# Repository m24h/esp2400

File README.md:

# esp2400

A digitalizing power supply control board woking with modified ZXD2400 (50V 50A) modoule.

This project is a control board mainly using ESP32 as core MPU, with ST7789V display,
including software source codes, hardware design, and other parts design,
to control a simply modified ZXD2400 power supply module.

In fact, this project is suitable for modifying other power supply module too.

its main functions include:
. 0-50.00V and 0-50.00A output with internal 14bits resolution
. Multi-points calibration of voltage and current.
. Two EC11 rotaries to control voltage and current separately
. Multi quick-pick of voltage and current by single pressing button
. Statistics by seconds, minutes, hours
. WIFI STA and AP support with a simple web view for remote control
. Command line support with USB-Serial interface (also firmware updating interface)
. Temperature controlled FAN output using PID algorithm
. A discharging circuit to decrease dormancy of switching power supply at low-voltage outputing
. Rate of rising and falling of voltage and current can be controlled
. Chinese and English bundles support (but in fact, original ZXD2400 with its PFC circiut can be used in AC220V zones)

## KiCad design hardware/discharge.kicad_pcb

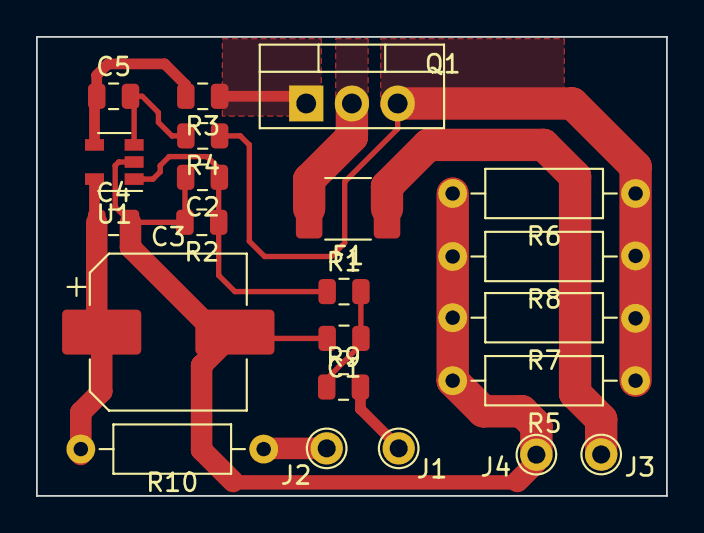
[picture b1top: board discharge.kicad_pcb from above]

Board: 2 copper layers, 35.0 x 25.5 mm, 22 parts (0 on the bottom side), 12 nets.

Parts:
C1: 0.47; C_0805_2012Metric
C2: 1; C_0805_2012Metric
C3: 100/25v; CP_Elec_8x10.5
C4: 0.1; C_0805_2012Metric
C5: 2n; C_0805_2012Metric
F1: 2.6A; Fuse_1812_4532Metric_Castellated
J1, J2, J3, J4: PAD; Pad
Q1: FHP40N20; TO-220-3_Vertical
R1, R4, R9: 10k; R_0805_2012Metric
R2: 2.2k; R_0805_2012Metric
R3: 1k; R_0805_2012Metric
R5, R7: 1/0.25w; R_Axial_DIN0207_L6.3mm_D2.5mm_P10.16mm_Horizontal
R6, R8: 1/0.25W; R_Axial_DIN0207_L6.3mm_D2.5mm_P10.16mm_Horizontal
R10: 47/0.25W; R_Axial_DIN0207_L6.3mm_D2.5mm_P10.16mm_Horizontal
U1: LM321; SOT-23-5

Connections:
unnamed: C1.1, R1.2, R9.1
unnamed: C1.2, C2.2, C3.2, C4.2, J4.1, R2.2, R5.2, R6.2, R7.2, R8.2, U1.2
unnamed: C2.1, R1.1, R2.1, U1.1
unnamed: C3.1, C4.1, R10.2, U1.5
unnamed: C5.1, R3.2, U1.4
unnamed: C5.2, R4.2, U1.3
unnamed: F1.1, J3.1
unnamed: F1.2, Q1.2
unnamed: J1.1, R9.2
unnamed: J2.1, R10.1
unnamed: Q1.1, R3.1
unnamed: Q1.3, R4.1, R5.1, R6.1, R7.1, R8.1

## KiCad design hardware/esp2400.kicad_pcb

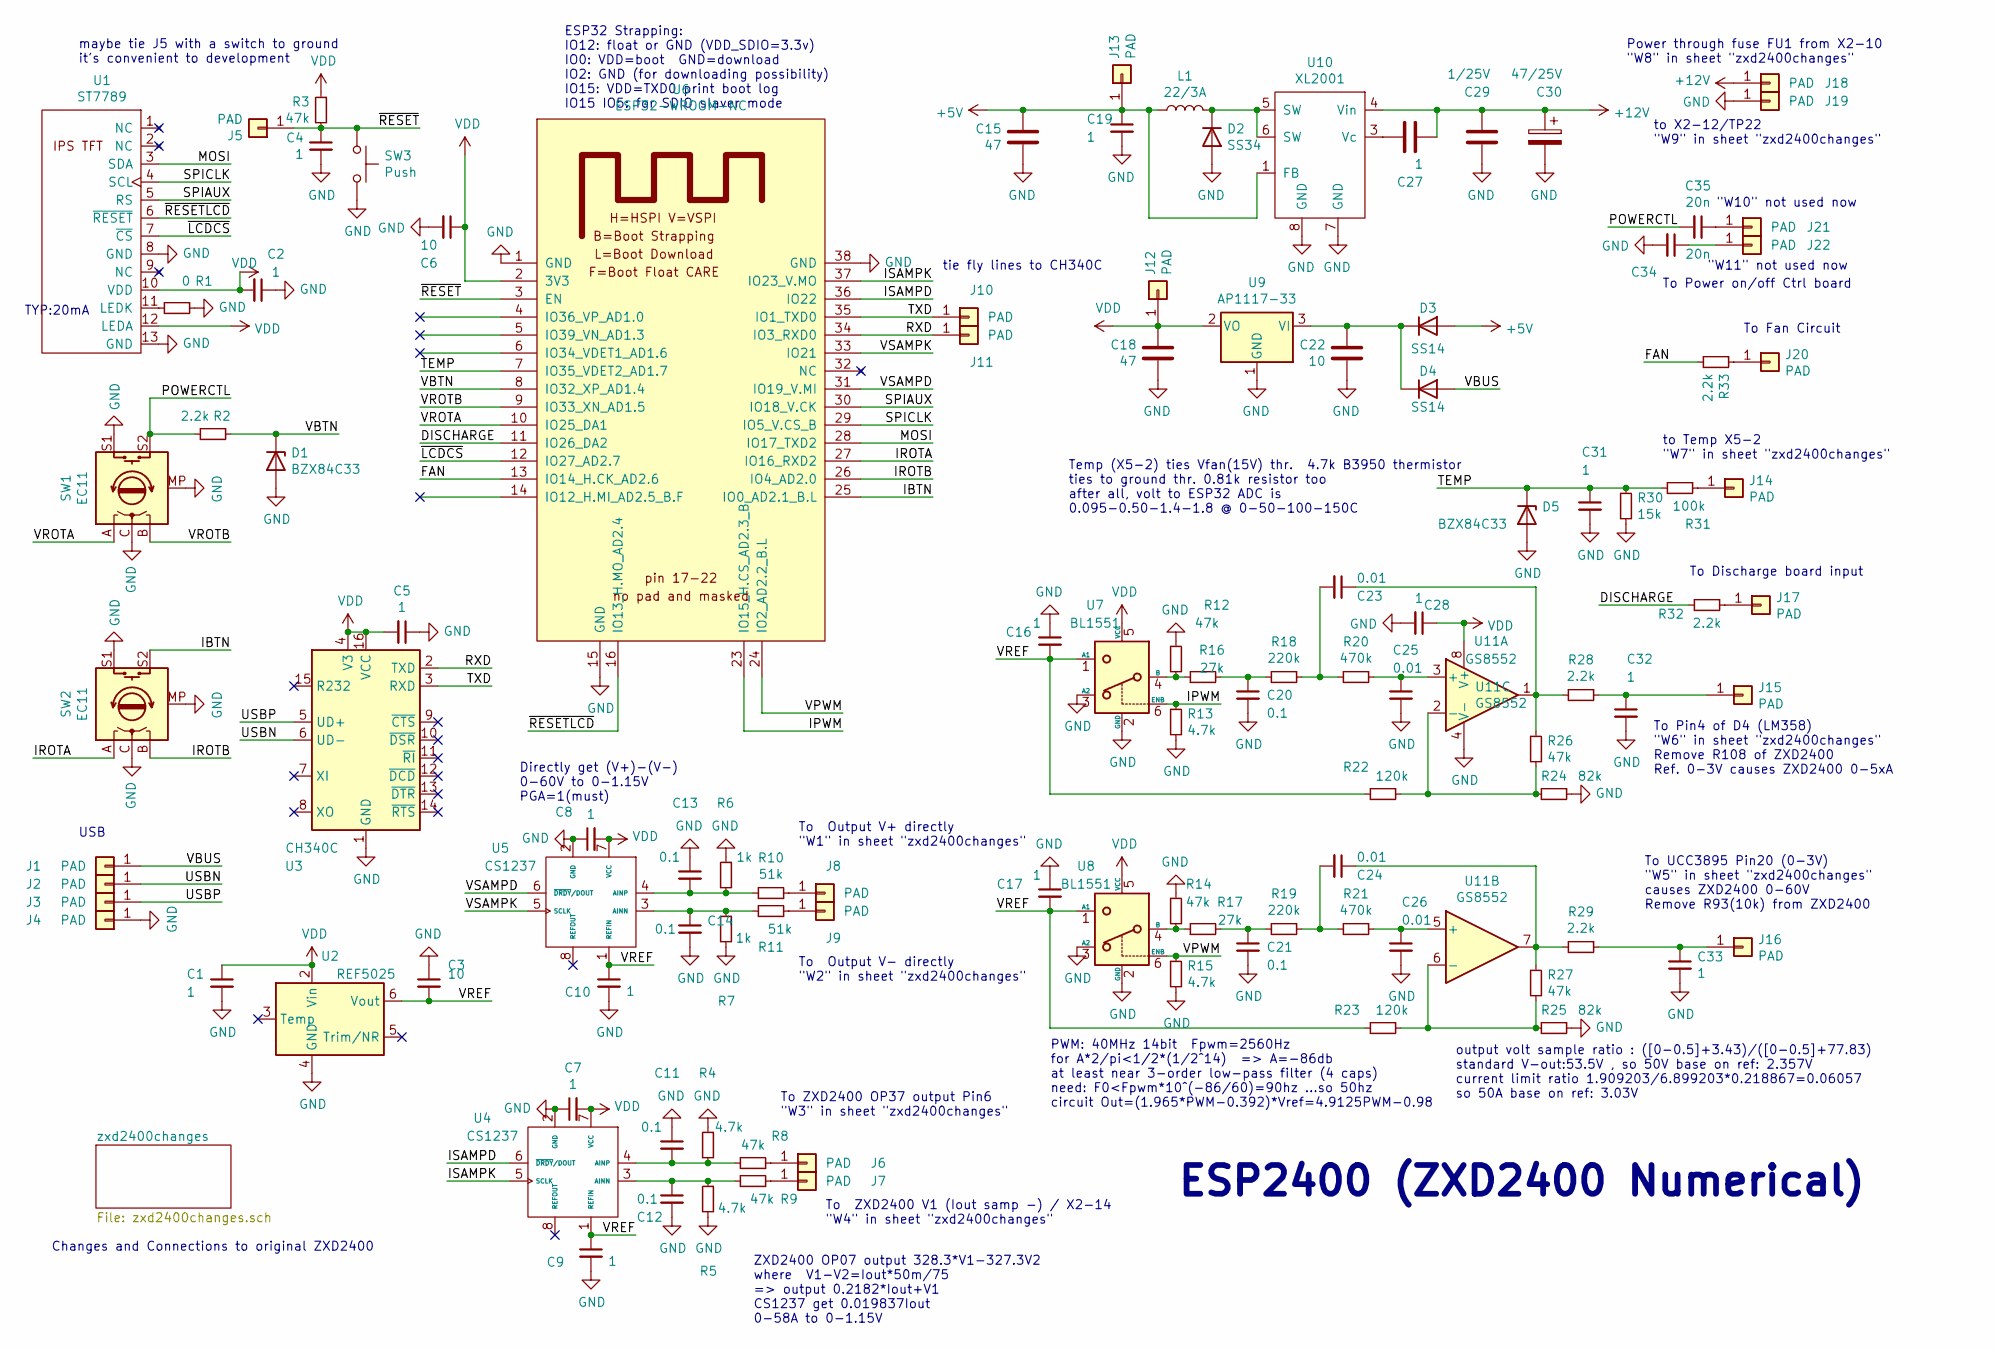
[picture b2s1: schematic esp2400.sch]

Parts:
C1, C2, C4, C5, C7, C8, C9, C10, C16, C17, C19, C27, C28, C31, C32, C33: 1; C_0805_2012Metric
C3, C6, C22: 10; C_0805_2012Metric
C11, C12, C13, C14, C20, C21: 0.1; C_0603_1608Metric
C15, C18: 47; C_1210_3225Metric
C23, C24, C25, C26: 0.01; C_0603_1608Metric
C29: 1/25V; C_1206_3216Metric
C30: 47/25V; CP_Elec_5x5.9
C34, C35: 20n; C_0805_2012Metric
D1, D5: BZX84C33; D_SOT-23_ANK
D2: SS34; D_SMB
D3, D4: SS14; D_SMA
J1, J2, J3, J4, J5, J6, J7, J8, J9, J10, J11, J12, J13, J14, J15, J16, J17, J18, J19, J20, J21, J22: PAD; Pad
L1: 22/3A; L_Bourns_SRP7028A_7.3x6.6mm
R1: 0; R_0805_2012Metric
R2, R28, R29, R32, R33: 2.2k; R_0603_1608Metric
R3, R8, R9, R12, R14, R26, R27: 47k; R_0603_1608Metric
R4, R5, R13, R15: 4.7k; R_0603_1608Metric
R6, R7: 1k; R_0603_1608Metric
R10, R11: 51k; R_0603_1608Metric
R16, R17: 27k; R_0603_1608Metric
R18, R19: 220k; R_0603_1608Metric
R20, R21: 470k; R_0603_1608Metric
R22, R23: 120k; R_0603_1608Metric
R24, R25: 82k; R_0603_1608Metric
R30: 15k; R_0603_1608Metric
R31: 100k; R_0603_1608Metric
SW1, SW2: EC11; RotaryEncoder_Alps_EC11E-Switch_Vertical_H20mm
SW3: Push; SW_Push_1P1T_NO_CK_KSC6xxJ
U1: ST7789; 1.14LCD
U2: REF5025; SOIC-8_3.9x4.9mm_P1.27mm
U3: CH340C; SOP-16_4.4x10.4mm_P1.27mm
U4, U5: CS1237; SOP-8_3.9x4.9mm_P1.27mm
U6: ESP32-WROOM-NC
U7, U8: BL1551; SC70-6
U9: AP1117-33; SOT-223-3_TabPin2
U10: XL2001; SOIC-8_3.9x4.9mm_P1.27mm
U11: GS8552; SOIC-8_3.9x4.9mm_P1.27mm

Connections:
+5V: C15.1, C19.1, D3.2 (A), J13.1, L1.2, U10.1 (FB)
+12V: C27.2, C29.1, C30.1, J18.1, U10.4 (Vin)
/DISCHARGE: R32.2, U6.11 (IO26_DA2)
/FAN: R33.2, U6.13 (IO14_H.CK_AD2.6)
/IBTN: SW2.S2, U6.25 (IO0_AD2.1_B.L)
/IPWM: R13.1, U6.23 (IO15_H.CS_AD2.3_B), U7.6 (ENB)
/IROTA: SW2.A, U6.27 (IO16_RXD2)
/IROTB: SW2.B, U6.26 (IO4_AD2.0)
/ISAMPD: U4.6 (~DRDY~/DOUT), U6.36 (IO22)
/ISAMPK: U4.5 (SCLK), U6.37 (IO23_V.MO)
/MOSI: U1.3 (SDA), U6.28 (IO17_TXD2)
/POWERCTL: C35.2, R2.2, SW1.S2
/RXD: J11.1, U3.2 (TXD), U6.34 (IO3_RXD0)
/SPIAUX: U1.5 (RS), U6.30 (IO18_V.CK)
/SPICLK: U1.4 (SCL), U6.29 (IO5_V.CS_B)
/TEMP: C31.1, D5.1 (K), R30.1, R31.2, U6.7 (IO35_VDET2_AD1.7)
/TXD: J10.1, U3.3 (RXD), U6.35 (IO1_TXD0)
/USBN: J2.1, U3.6 (UD-)
/USBP: J3.1, U3.5 (UD+)
/VBTN: D1.1 (K), R2.1, U6.8 (IO32_XP_AD1.4)
/VBUS: D4.2 (A), J1.1
/VPWM: R15.1, U6.24 (IO2_AD2.2_B.L), U8.6 (ENB)
/VREF: C3.2, C9.1, C10.1, C16.2, C17.2, R22.2, R23.2, U2.6 (Vout), U4.1 (REFIN), U5.1 (REFIN), U7.1 (A1), U8.1 (A1)
/VROTA: SW1.A, U6.10 (IO25_DA1)
/VROTB: SW1.B, U6.9 (IO33_XN_AD1.5)
/VSAMPD: U5.6 (~DRDY~/DOUT), U6.31 (IO19_V.MI)
/VSAMPK: U5.5 (SCLK), U6.33 (IO21)
/~LCDCS: U1.7 (~CS), U6.12 (IO27_AD2.7)
/~RESET: C4.1, J5.1, R3.2, SW3.1, U6.3 (EN)
/~RESETLCD: U1.6 (~RESET), U6.16 (IO13_H.MO_AD2.4)
GND: C1.2, C2.1, C3.1, C4.2, C5.1, C6.2, C7.1, C8.1, C9.2, C10.2, C11.1, C12.2, C13.1, C14.2, C15.2, C16.1, C17.1, C18.2, C19.2, C20.2, C21.2, C22.2, C25.2, C26.2, C28.2, C29.2, C30.2, C31.2, C32.2, C33.2, C34.2, D1.2 (A), D2.2 (A), D5.2 (A), J4.1, J19.1, R1.1, R4.1, R5.2, R6.1, R7.2, R12.1, R13.2, R14.1, R15.2, R24.1, R25.1, R30.2, SW1.C, SW1.MP, SW1.S1, SW2.C, SW2.MP, SW2.S1, SW3.2, U1.8 (GND), U1.13 (GND), U2.4 (GND), U3.1 (GND), U4.2 (GND), U5.2 (GND), U6.1 (GND), U6.15 (GND), U6.38 (GND), U7.2 (GND), U7.3 (A2), U8.2 (GND), U8.3 (A2), U9.1 (GND), U10.7 (GND), U10.8 (GND), U11.4 (V-)
unnamed: C11.2, R4.2, R8.2, U4.4 (AINP)
unnamed: C12.1, R5.1, R9.2, U4.3 (AINN)
unnamed: C13.2, R6.2, R10.2, U5.4 (AINP)
unnamed: C14.1, R7.1, R11.2, U5.3 (AINN)
unnamed: C20.1, R16.2, R18.2
unnamed: C21.1, R17.2, R19.2
unnamed: C22.1, D3.1 (K), D4.1 (K), U9.3 (VI)
unnamed: C23.1, R26.1, R28.2, U11.1
unnamed: C23.2, R18.1, R20.2
unnamed: C24.1, R27.1, R29.2, U11.7
unnamed: C24.2, R19.1, R21.2
unnamed: C25.1, R20.1, U11.3 (+)
unnamed: C26.1, R21.1, U11.5 (+)
unnamed: C27.1, U10.3 (Vc)
unnamed: C32.1, J15.1, R28.1
unnamed: C33.1, J16.1, R29.1
unnamed: C34.1, J22.1
unnamed: C35.1, J21.1
unnamed: D2.1 (K), L1.1, U10.5 (SW), U10.6 (SW)
unnamed: J6.1, R8.1
unnamed: J7.1, R9.1
unnamed: J8.1, R10.1
unnamed: J9.1, R11.1
unnamed: J14.1, R31.1
unnamed: J17.1, R32.1
unnamed: J20.1, R33.1
unnamed: R1.2, U1.11 (LEDK)
unnamed: R12.2, R16.1, U7.4 (B)
unnamed: R14.2, R17.1, U8.4 (B)
unnamed: R22.1, R24.2, R26.2, U11.2 (-)
unnamed: R23.1, R25.2, R27.2, U11.6 (-)
VDD: C1.1, C2.2, C5.2, C6.1, C7.2, C8.2, C18.1, C28.1, J12.1, R3.1, U1.10 (VDD), U1.12 (LEDA), U2.2 (Vin), U3.4 (V3), U3.16 (VCC), U4.7 (VCC), U5.7 (VCC), U6.2 (3V3), U7.5 (VCC), U8.5 (VCC), U9.2 (VO), U11.8 (V+)

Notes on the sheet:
TYP:20mA
Power through fuse FU1 from X2-10 "W8" in sheet "zxd2400changes"
To Fan Circuit
to X2-12/TP22 "W9" in sheet "zxd2400changes"
To Discharge board input
To UCC3895 Pin20 (0-3V) "W5" in sheet "zxd2400changes" causes ZXD2400 0-60V Remove R93(10k) from ZXD2400
ESP32 Strapping: IO12: float or GND (VDD_SDIO=3.3v) IO0: VDD=boot GND=download IO2: GND (for downloading possibility) IO15: VDD=TXD0 print boot log IO15 IO5: for SDIO slaver mode
PWM: 40MHz 14bit Fpwm=2560Hz for A*2/pi<1/2*(1/2^14) => A=-86db at least near 3-order low-pass filter (4 caps) need: F0<Fpwm*10^(-86/60)=90hz ...so 50hz circuit Out=(1.965*PWM-0.392)*Vref=4.9125PWM-0.98
To Output V+ directly "W1" in sheet "zxd2400changes"
To Output V- directly "W2" in sheet "zxd2400changes"
To ZXD2400 OP37 output Pin6 "W3" in sheet "zxd2400changes"
To ZXD2400 V1 (Iout samp -) / X2-14 "W4" in sheet "zxd2400changes"
Directly get (V+)-(V-) 0-60V to 0-1.15V PGA=1(must)
ZXD2400 OP07 output 328.3*V1-327.3V2 where V1-V2=Iout*50m/75 => output 0.2182*Iout+V1 CS1237 get 0.019837Iout 0-58A to 0-1.15V
To Power on/off Ctrl board
ESP2400 (ZXD2400 Numerical)
to Temp X5-2 "W7" in sheet "zxd2400changes"
To Pin4 of D4 (LM358) "W6" in sheet "zxd2400changes" Remove R108 of ZXD2400 Ref. 0-3V causes ZXD2400 0-5xA
USB
Temp (X5-2) ties Vfan(15V) thr. 4.7k B3950 thermistor ties to ground thr. 0.81k resistor too after all, volt to ESP32 ADC is 0.095-0.50-1.4-1.8 @ 0-50-100-150C
output volt sample ratio : ([0-0.5]+3.43)/([0-0.5]+77.83) standard V-out:53.5V , so 50V base on ref: 2.357V current limit ratio 1.909203/6.899203*0.218867=0.06057 so 50A base on ref: 3.03V
Changes and Connections to original ZXD2400
maybe tie J5 with a switch to ground it's convenient to development
tie fly lines to CH340C
"W10" not used now
"W11" not used now

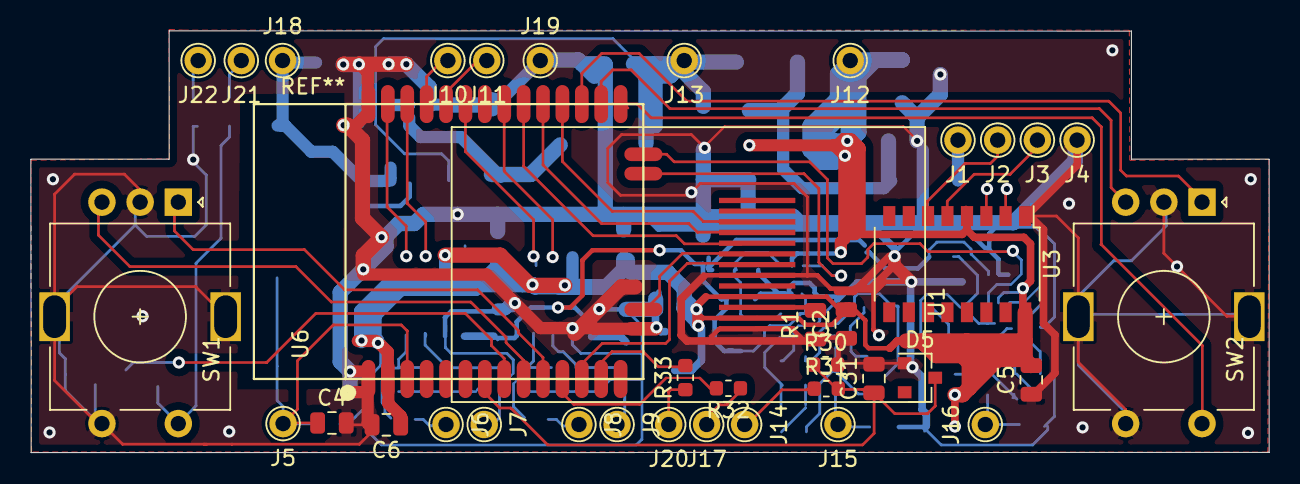
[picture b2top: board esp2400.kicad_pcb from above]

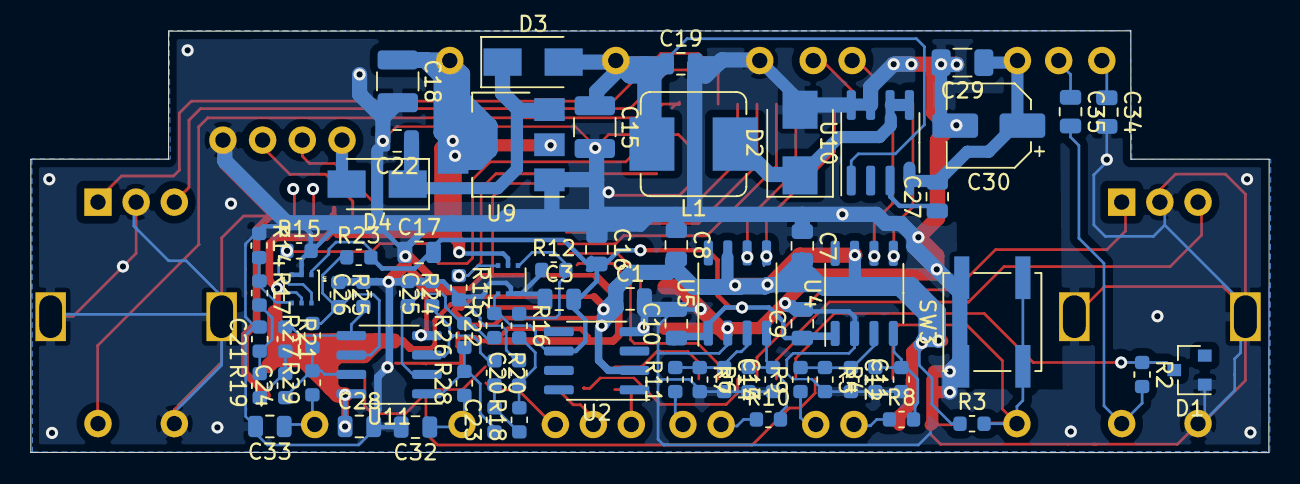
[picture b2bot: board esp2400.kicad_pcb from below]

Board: 2 copper layers, 81.1 x 27.6 mm, 110 parts (72 on the bottom side), 63 nets.

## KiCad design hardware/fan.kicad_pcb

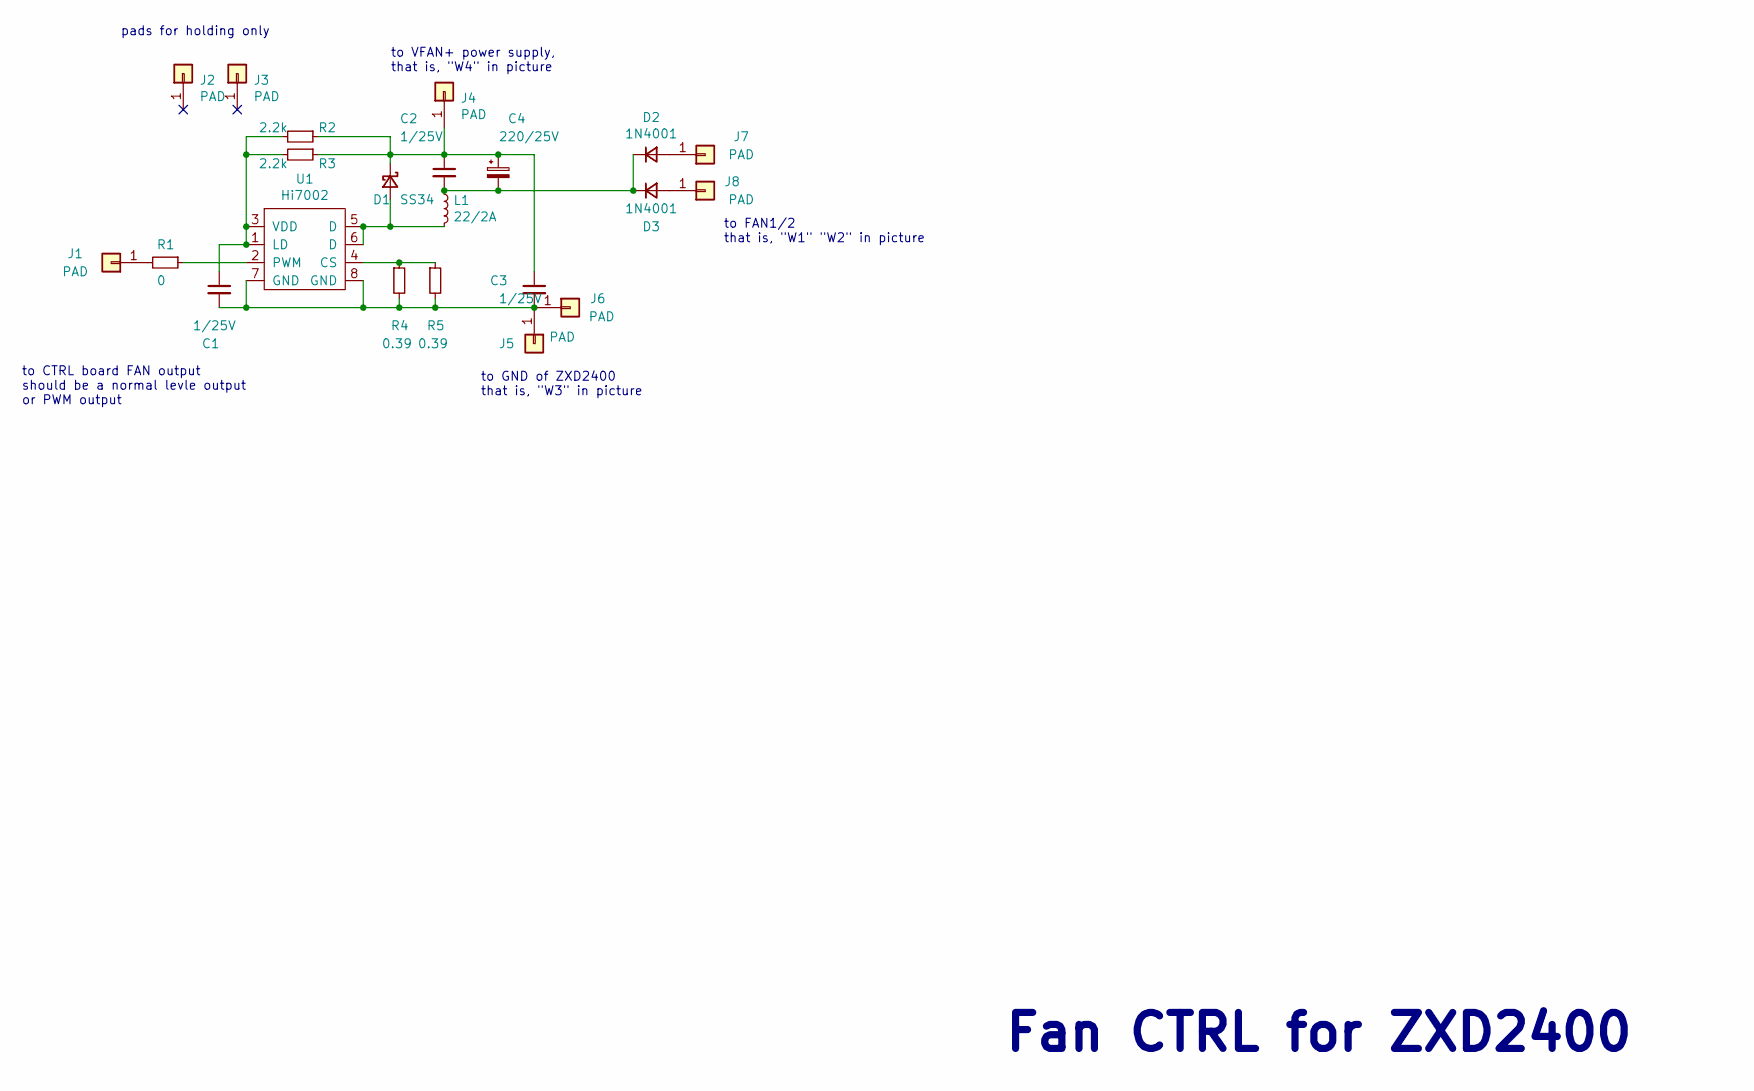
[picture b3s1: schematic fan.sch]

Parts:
C1, C2, C3: 1/25V; C_0805_2012Metric
C4: 220/25V; CP_Radial_D6.3mm_P2.50mm
D1: SS34; D_SMB
D2, D3: 1N4001; D_DO-41_SOD81_P7.62mm_Horizontal
J1, J2, J3, J4, J5, J6, J7, J8: PAD; Pad-big
L1: 22/2A; L_Bourns_SRP7028A_7.3x6.6mm
R1: 0; R_0805_2012Metric
R2, R3: 2.2k; R_0805_2012Metric
R4, R5: 0.39; R_1206_3216Metric
U1: Hi7002; SOP-8_3.9x4.9mm_P1.27mm

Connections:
unnamed: C1.1, R2.2, R3.2, U1.1 (LD), U1.3 (VDD)
unnamed: C1.2, C3.2, J5.1, J6.1, R4.2, R5.2, U1.7 (GND), U1.8 (GND)
unnamed: C2.1, C3.1, C4.1, D1.1 (K), J4.1, R2.1, R3.1
unnamed: C2.2, C4.2, D2.1 (K), D3.1 (K), L1.1
unnamed: D1.2 (A), L1.2, U1.5 (D), U1.6 (D)
unnamed: D2.2 (A), J7.1
unnamed: D3.2 (A), J8.1
unnamed: J1.1, R1.2
unnamed: R1.1, U1.2 (PWM)
unnamed: R4.1, R5.1, U1.4 (CS)

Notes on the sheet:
Fan CTRL for ZXD2400
to GND of ZXD2400 that is, "W3" in picture
to FAN1/2 that is, "W1" "W2" in picture
to CTRL board FAN output should be a normal levle output or PWM output
pads for holding only
to VFAN+ power supply, that is, "W4" in picture

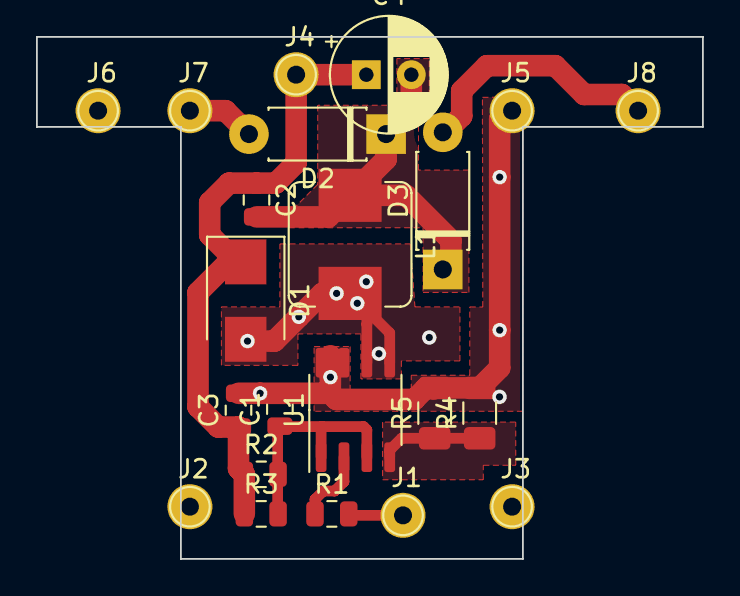
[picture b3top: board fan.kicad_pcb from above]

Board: 2 copper layers, 37.0 x 29.0 mm, 22 parts (0 on the bottom side), 10 nets.

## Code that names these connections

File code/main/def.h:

/**
 * Know nothing about copy from left to right,
 * if someone wanna use it, just copy it from left to right
 *                by author m24h
 */
#pragma once

#ifdef __cplusplus
extern "C" {
#endif

#define VERSION         1
#define REVISION        "Zero"

#define VFAN            15.5   /* Vfan for calculate temperature, in Volt, can be double */

#define ADC1_CHAN_TEMP  7 /* ADC1.7, GPIO pin 35 */

#define PIN_FAN        14
#define PIN_DISCHARGE  26
#define DAC_DISCHARGE  DAC_CHANNEL_2

#define PIN_SPICLK    5
#define PIN_MOSI     17
#define PIN_SPIAUX   18
#define PIN_LCDCS    27
#define PIN_RESETLCD 13

#define PIN_IROTA 16
#define PIN_IROTB  4
#define PIN_IBTN   0

#define PIN_VROTA 25
#define PIN_VROTB 33
#define PIN_VBTN  32

#define PIN_ISAMPK 23
#define PIN_ISAMPD 22

#define PIN_VSAMPK 21
#define PIN_VSAMPD 19

#define PIN_IPWM  15
#define PIN_VPWM   2

#define PIN_UART_TX 1
#define PIN_UART_RX 3

#define ROTARY_TYPE  0 /* 0: one pulse per step, 1: half pulse per step, 2:as 0 but cw/ccw reversed, 3:as 1 but cw/ccw reversed */
#define BTN_LONGTIME 1200000 /* 1.2s in micro-second */

#define V_MAX 50000  /* in mV */
#define V_MIN 0      /* in mV */
#define V_OFF 0      /* in mV */
#define I_MAX 50000  /* in mA */
#define I_MIN 0      /* in mA */
#define I_OFF 0      /* in mA */

#define STAT_SIZE     128  /* statistics point number of every second, minute, hour */
#define QUICK_POINTS   27  /* store favorite v/i points to load */

/* default calibration between mV/mA and 0-2^31 scope int32 */
#define CAL_POINTS             16   /* how many calibration points can be set */
#define CAL_ISAMP_MIN           0   /* default I sampling calibration point for I_MIN */
#define CAL_ISAMP_MAX  1709139286   /* default I sampling calibration point for I_MAX */
#define CAL_VSAMP_MIN           0   /* default V sampling calibration point for V_MIN */
#define CAL_VSAMP_MAX  1684300900   /* default V sampling calibration point for V_MIN */
#define CAL_IOUT_MIN    428403863   /* default I output calibration point for I_MIN */
#define CAL_IOUT_MAX   1752958662   /* default I output calibration point for I_MIN */
#define CAL_VOUT_MIN    428403863   /* default V output calibration point for V_MIN */
#define CAL_VOUT_MAX   1458758867   /* default V output calibration point for V_MIN */

#define DISCHARGE_PWM           0  /* use PWM discharge output */
#define DISCHARGE_DAC           1  /* use PWM discharge output */
#define DISCHARGE_BASE       3000  /* if output voltage is below this, discharge fully at nearly 1.3A, now my PWM circuit can only hold 4W */

/*
 *  KP/KA is weights for PID feat. Current Controlling FAN, can be double
 *  KP=1 means full fan output when temperature is nearly 1 degree higher
 *  KA=1 means full fan output when current is nearly I_MAX
 *  unit of TI/TD/TF is second, can be double
 */
#define FAN_KP 0.15
#define FAN_KA 0.3
#define FAN_TI 150
#define FAN_TD   2
#define FAN_TF  10
#define FAN_PWM                 1  /* use PWM fan output */

#define MAX_RECOVERABLE_FAILURES 50 /* continuous recoverable failures will cause reset */
#define WATCH_DOG_TIME     5

#define MAIN_STACK      4096
#define MAIN_CORE       1
#define MAIN_PRIORITY   5
#define MAIN_PERIOD_MS  30  /* do a sampling/output/statistics every period */

#define REPL_STACK      4096
#define REPL_CORE       tskNO_AFFINITY
#define ELOOP_QUEUE     64
#define ELOOP_STACK     4096
#define ELOOP_CORE      tskNO_AFFINITY
#define HTTPD_STACK     6144
#define HTTPD_CORE      tskNO_AFFINITY
#define HTTPD_HANDLERS  8
#define HTTPD_PORT      80
#define HTTPD_DEF_FILE  "index.htm"  /* wl fatfsgen support only 8.3 file name */

#define FS_PATH_SIZE        256 /* include '\0' at tail */
#define FS_STORAGE_OPENMAX  6
#define FS_STORAGE_PAR      "storage"
#define FS_STORAGE_MNT      "/storage"
#define FS_CONF_FILE        FS_STORAGE_MNT "/app.cfg"
#define FS_REPL_HISTORY     FS_STORAGE_MNT "/repl.his"
#define FS_LOG_FILE         FS_STORAGE_MNT "/app%d.log"
#define FS_LOG_FILE_NUM     10  /* will use 0.log - 9.log */

#define FS_RESOURCE_OPENMAX 20/* mostly for web server */
#define FS_RESOURCE_PAR    "resource"
#define FS_RESOURCE_MNT    "/resource"
#define FS_DIR_WEB          FS_RESOURCE_MNT "/web"

/* Terminator colors used by REPL, not to modify*/
#define TERM_NO_SETTING       0
#define TERM_HIGHT_LIGHT      1
#define TERM_UNDERLINE        4
#define TERM_BLINK            5
#define TERM_INVERT           7
#define TERM_FADE             8
#define TERM_COLOR_BLACK     30
#define TERM_COLOR_RED       31
#define TERM_COLOR_GREEN     32
#define TERM_COLOR_YELLOW    33
#define TERM_COLOR_BLUE      34
#define TERM_COLOR_PURPLE    35
#define TERM_COLOR_CYAN      36
#define TERM_COLOR_WHITE     37
#define TERM_BGCOLOR_BLACK   40
#define TERM_BGCOLOR_RED     41
#define TERM_BGCOLOR_GREEN   42
#define TERM_BGCOLOR_YELLOW  43
#define TERM_BGCOLOR_BLUE    44
#define TERM_BGCOLOR_PURPLE  45
#define TERM_BGCOLOR_CYAN    46
#define TERM_BGCOLOR_WHITE   47

#define REPL_PROMPT          "\033[32mzxd2400>\033[0m "
#define REPL_PROMPT_NO_ESC   "zxd2400> "
#define REPL_HINT_COLOR      TERM_COLOR_YELLOW
#define REPL_LINE_MAX        256
#define REPL_ARGS_MAX        16
#define REPL_HISTORY_LINES   0

#define COLOR_BG          0x000000
#define COLOR_IC          0xFF0000
#define COLOR_IS          0xFF8080
#define COLOR_VC          0x00FF00
#define COLOR_VS          0x80FF80
#define COLOR_OFF         0x303030
#define COLOR_IT          0xB80000
#define COLOR_VT          0x00B800
#define COLOR_PT          0xB8B800
#define COLOR_ET          0x00B8B8
#define COLOR_TEMP        0x0000DF
#define COLOR_MESSAGE     0xC0C0C0
#define COLOR_SIGN        0xC0C000
#define COLOR_MENU        0xC0C0C0
#define COLOR_MENUHL      0xFFFF00
#define COLOR_MENUHINT    0x00D0D0

#ifdef __cplusplus
}
#endif

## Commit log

2022-01-13 first usable version
